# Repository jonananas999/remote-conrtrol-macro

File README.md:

# remote-conrtrol-macro
My macro remote control PCB design and future devolopment

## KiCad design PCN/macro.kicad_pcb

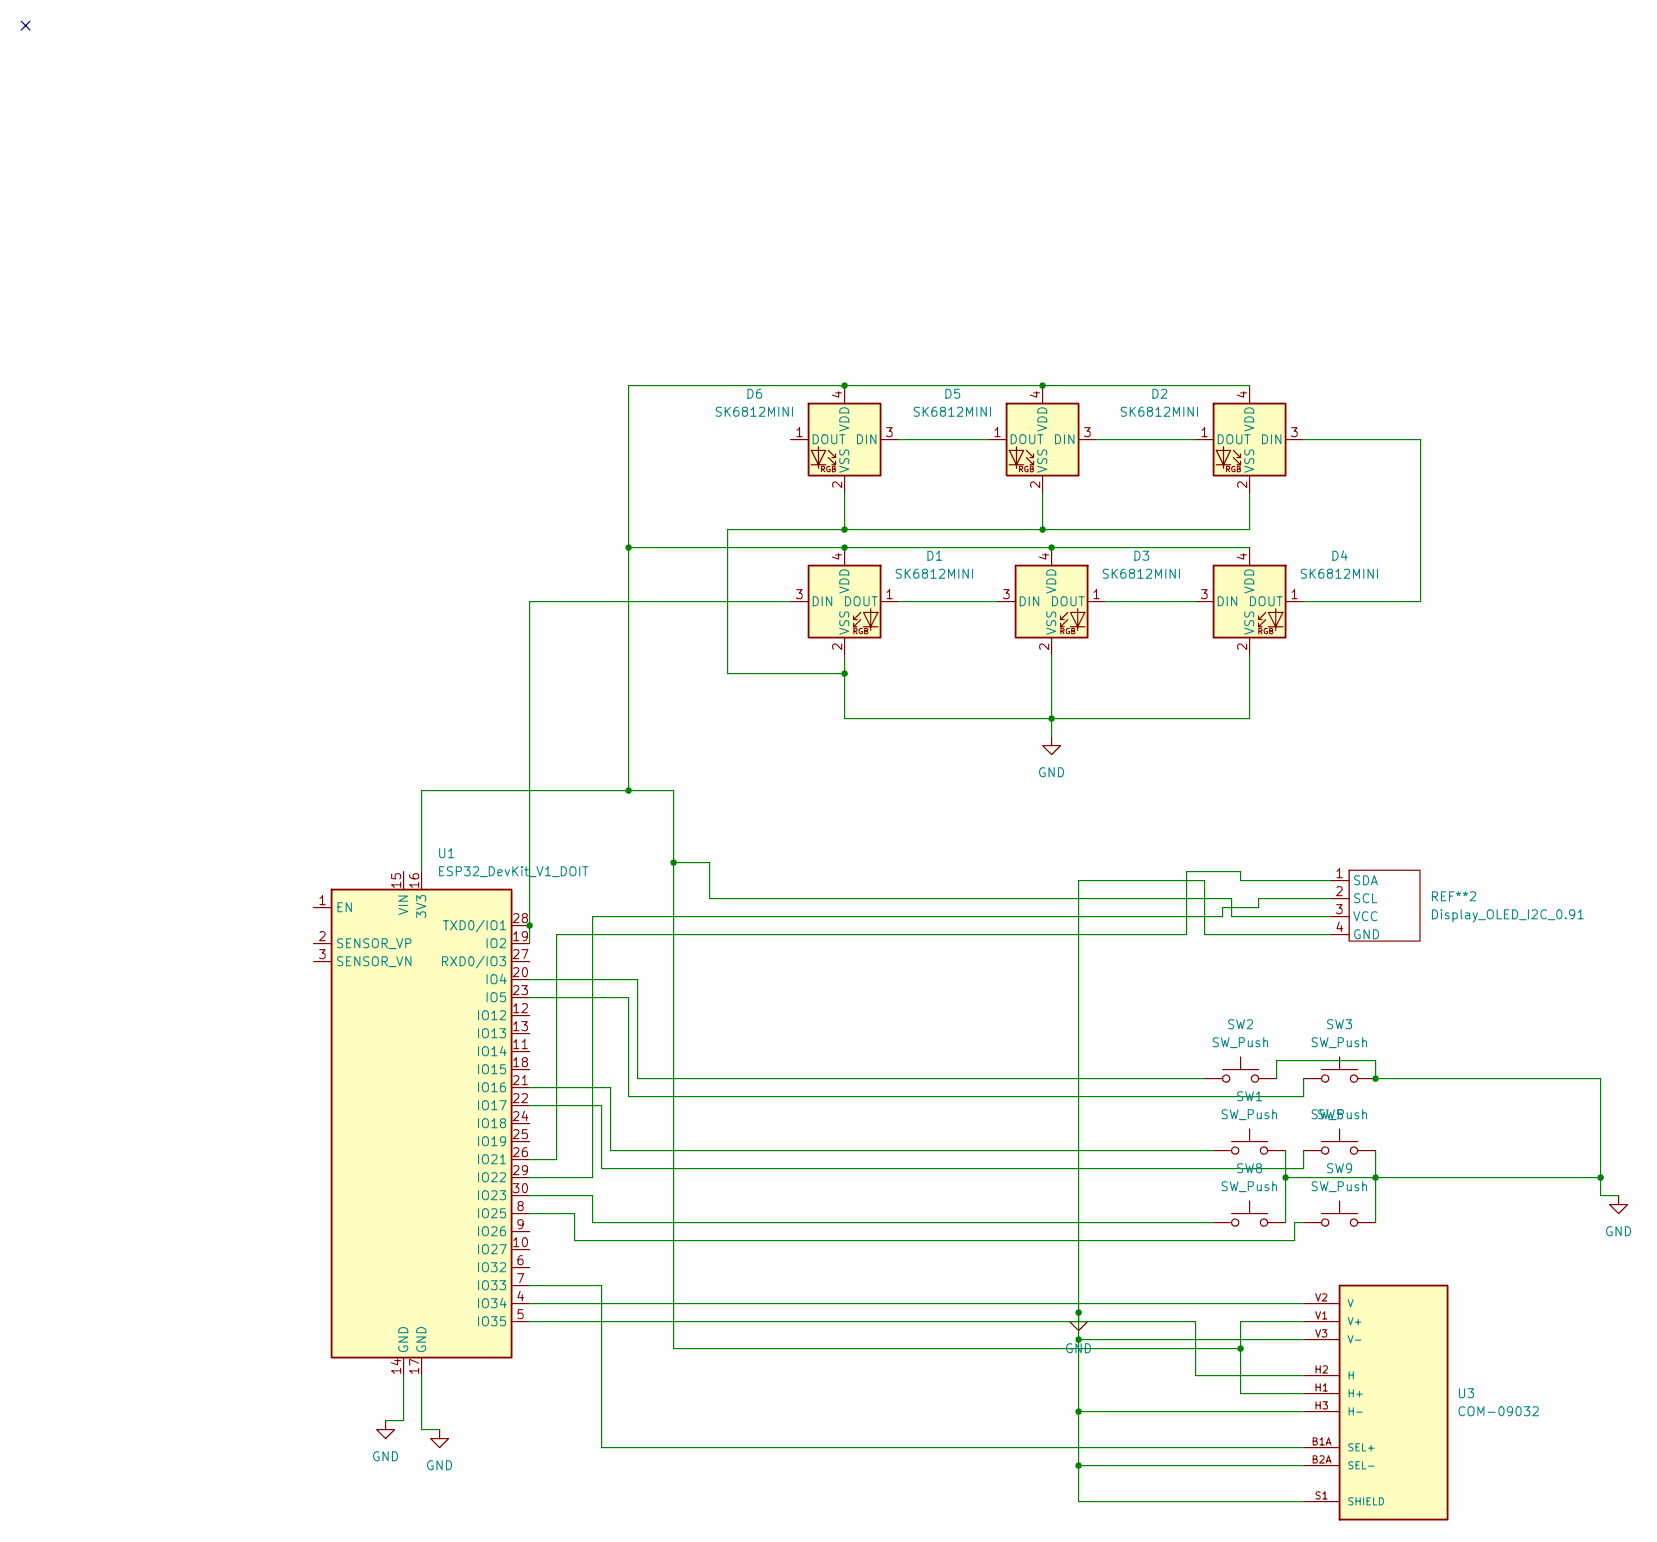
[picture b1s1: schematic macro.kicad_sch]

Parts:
D1, D2, D3, D4, D5, D6: SK6812MINI; LED_SK6812MINI_PLCC4_3.5x3.5mm_P1.75mm
REF**2: Display_OLED_I2C_0.91; OLED_0.91_I2C_1x04_P2.54mm
SW1, SW2, SW3, SW5, SW8, SW9: SW_Push; SW_Cherry_MX_1.00u_PCB
U1: ESP32_DevKit_V1_DOIT; esp32_devkit_v1_doit
U3: COM-09032; XDCR_COM-09032; PARTREV N/A

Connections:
GND: D1.2 (VSS), D2.2 (VSS), D3.2 (VSS), D4.2 (VSS), D5.2 (VSS), D6.2 (VSS), REF**2.4 (GND), SW1.2, SW2.2, SW3.2, SW5.2, SW8.2, SW9.2, U1.14 (GND), U1.17 (GND), U3.B2A (SEL-), U3.H3 (H-), U3.S1 (SHIELD), U3.S2 (SHIELD), U3.S3 (SHIELD), U3.S4 (SHIELD), U3.V3 (V-)
unnamed: D1.3 (DIN), U1.19 (IO2), U1.28 (TXD0/IO1)
unnamed: D1.1 (DOUT), D3.3 (DIN)
unnamed: D1.4 (VDD), D2.4 (VDD), D3.4 (VDD), D4.4 (VDD), D5.4 (VDD), D6.4 (VDD), REF**2.3 (VCC), U1.16 (3V3), U3.H1 (H+), U3.V1 (V+)
unnamed: D2.3 (DIN), D4.1 (DOUT)
unnamed: D2.1 (DOUT), D5.3 (DIN)
unnamed: D3.1 (DOUT), D4.3 (DIN)
unnamed: D5.1 (DOUT), D6.3 (DIN)
unnamed: REF**2.2 (SCL), U1.29 (IO22)
unnamed: REF**2.1 (SDA), U1.26 (IO21)
unnamed: SW2.1, U1.20 (IO4)
unnamed: SW3.1, U1.23 (IO5)
unnamed: SW1.1, U1.21 (IO16)
unnamed: SW5.1, U1.22 (IO17)
unnamed: SW8.1, U1.30 (IO23)
unnamed: SW9.1, U1.8 (IO25)
unnamed: U1.7 (IO33), U3.B1A (SEL+)
unnamed: U1.4 (IO34), U3.V2 (V)
unnamed: U1.5 (IO35), U3.H2 (H)

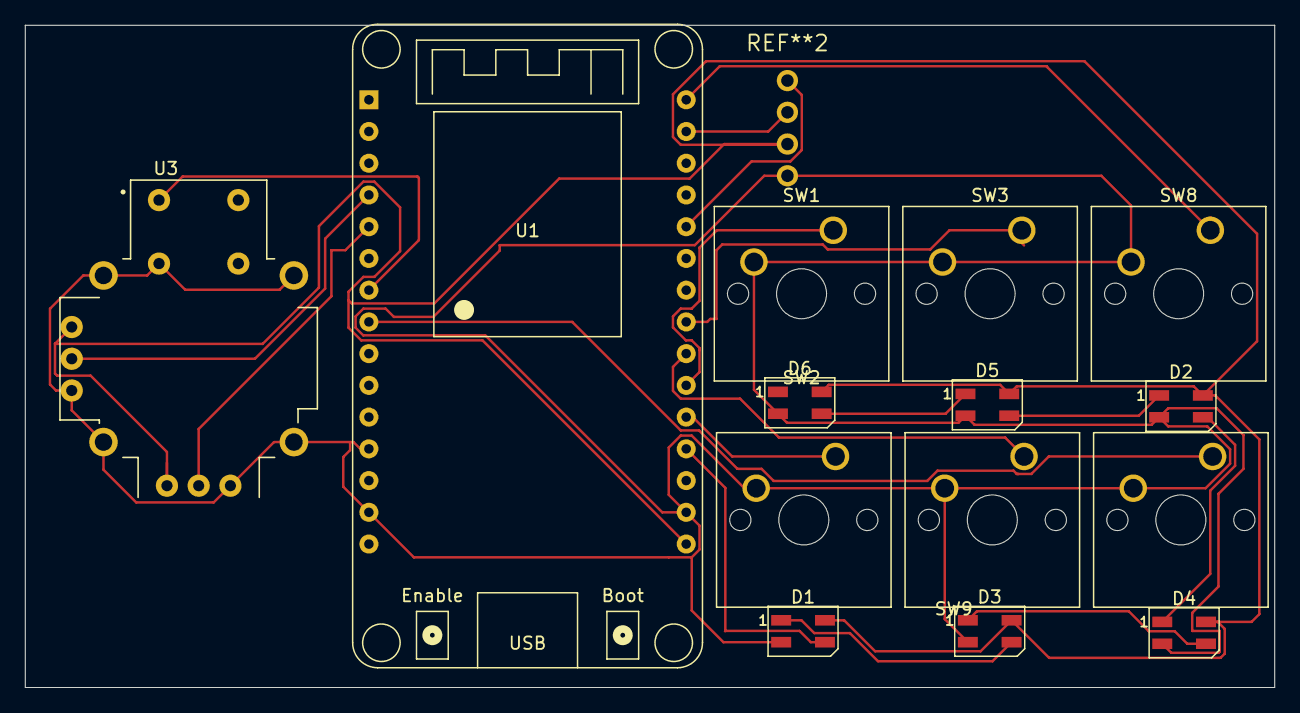
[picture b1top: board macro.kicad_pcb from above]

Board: 2 copper layers, 100.0 x 53.0 mm, 14 parts (0 on the bottom side), 17 nets.

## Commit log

2026-03-15 Create d
2026-03-15 Create fg
2026-03-15 Create sd
2026-03-15 Rename macro.kicad_pcb to macro.kicad_pcb
2026-03-15 Rename macro.kicad_pro to macro.kicad_pro
2026-03-15 Rename macro.kicad_sch to macro.kicad_sch
